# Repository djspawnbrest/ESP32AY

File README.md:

# ZxPod - multiformat Turbo Sound player
ESP32 based AY Turbo Sound multiformat player

## Fast flash firmware avaliable on [Alex Spawn OTA web page](https://ota.alexspawn.ru)

## Starting with firmware version 3.41 - added support for external DAC's - read [External DAC](PCB/ExternalDAC)

## IMPORTANT:
Firmwares from version 3.4 supports only PCB revision C! But you can soldering upgrade revision A and B to C:

Cut JP1 jumper on revisions A and B first!

### From rev.A to B and C:
You need to cut the input track on the resistor R33(see Pic.2) and solder the wire from the ESP32 (see Pic.1) to the cut contact of the resistor. See the images below.

### From rev. A and B to C:
You need to cut the tracks as shown in Figure 5 (red cut lines), then carefully strip the tracks from the solder mask and solder the wires (green lines) to the ESP32.

## Features
### Supported formats:
- .ayl - [Ay_Emul](https://bulba.untergrund.net/emulator_e.htm) by Sergey Bulba own playlist format
- .pt1 - Pro Tracker v1 file format
- .pt2 - Pro Tracker v2 file format
- .pt3 - Pro Tracker v3 (include Turbo Sound on two AY chips) file format
- .stc - Sound Tracker file format
- .stp - Sound Tracker Pro file format
- .asc - Sound Master file format 
- .psc - Pro Sound Creator file format
- .sqt - SQ Tracker file format
- .ay  - AY file format
- .psg - Programmable Sound Generator file format
- .rsf - Registers Stream Flow file format
- .yrg - [Custom AVR-AY format](https://www.avray.ru/ru/avr-ay-player/)
- .mod - Amiga MOD tracker format designed for creating, storing and playing music on an Amiga PC
- .s3m - (Scream Tracker 3 Module) is a module file format, based on the original MOD format used on the Amiga computer.
- .xm  - The XM file format, also known as Extended Module, is a digital audio file type for music created in the FastTracker 2 software (rev.D and above only).
- .tap - A file format for emulating ZX Spectrum magnetic tape images, which stores data from standard Sinclair BASIC procedures for working with a cassette.
- .tzx - A file format used to store programs and games for the ZX Spectrum computer as audio data from magnetic tape.
- .mp3 - MP3 (MPEG-1 Audio Layer 3) is a widely used digital audio format that uses a lossy compression method to significantly reduce file size while maintaining near-CD quality audio.
- .wav - is an audio file format for storing uncompressed audio data, developed by Microsoft and IBM. It is known for high-quality audio that retains all original data, but results in large file sizes, making it popular for professional audio recording and editing. The format stores audio data in chunks and commonly uses linear pulse-code modulation (LPCM) for encoding.
- UART mode (available in player settings menu as Player source)
- SD forwarding via USB as Mass Storage device (rev.D and above only) (press left button("-") and turn ON player)

### Controls
- Before player turning on - hold left button and turn on player to enter root config (needed for change encoder type). Encoder types:
    1. STEP 4L - active low (pull-up to VCC). Full cycle (4 phases) per click.
    2. STEP 4H - active high (pull-up to GND). Full cycle (4 phases) per click
    3. STEP 2 - half cycle (2 phases) per click (Set by default)
    4. STEP 1 - quarter cycle (1 phase) per click, and non-latching encoders
- Before player turning on - hold right button and turn on player to reset config to default.
- Before player turning on - hold encoder button and turn on player to reset last playing track (if player freezes or reboot on this file).
- Encoder Hold - change mode player/file browser
- Encoder Click - in player mode - play/pause; in file browser mode select track/playlist/directory; select - in config mode
- Encoder Double click - in player mode - open settings
- Encoder Push and turn right - fast forward (for ay format change next subsong, for tape formats - change next block)
- Encoder Push and turn left - slow down (for ay format change previous subsong, for tape formats - change previous block)
- Left button click/hold - volume - (in player mode); cancel - in config mode
- Right button click/hold - volume + (in player mode)
- Left button double click - change AY clock (in player mode) for PSG formats or change stereo panning for formats over DAC (mod,s3m etc.)
- Right button double click - change play mode: all/shuffle/once (in player mode)
- Right button hold and encoder click - remove file (only files, only in file browser).
- Right button click - change file sorting in file browser. (only in file browser).

### Playing modes:
- Playing all tracks (in folder/playlist)
- Playing random track (in folder/playlist)
- Playing once track (loop)

### Supports fully realtime file browser

### Supports realtime AY layers change:
- ABC
- ACB
- BAC
- BCA
- CAB
- CBA

### Supports realtime AY clock change:
- ZX SPECTRUM - 1773400 Hz
- PENTAGON - 1750000 Hz
- MSX - 1789772 Hz
- CPC - 1000000 Hz
- ATARI ST - 2000000 Hz

### Built-in battery

### Built-in charger and indication on LED and TFT

### Built-in headphones stereo amplifier controlled by I2C bus

## Demo video with digital sound record:

### UPD 22.10.2024
- Add new feature: "UART mode" with AVR-AY player through UART.

### UPD 04.03.2025
- Add new formats: .mod and .s3m tracker module formats
- Change PCB to revision C

### UPD 18.06.2025
- Change PCB to revision D (ESP32 chip change to ESP32-S3 (N16R8) chip)

### UPD 16.07.2025
- SD forwarding via USB as Mass Storage device (rev.D and above only)

### UPD 12.09.2025
- Add .xm file format (rev.D and above only). Change Firmware version to 3.5

### UPD 15.10.2025
- Add .tap, .tzx formats to play and loads programms on ZX-Spectrum.

### UPD 08.10.2025
- Add .mp3, .wav formats.

### UPD 10.10.2025
- Add file sorting in file broser on right button click!

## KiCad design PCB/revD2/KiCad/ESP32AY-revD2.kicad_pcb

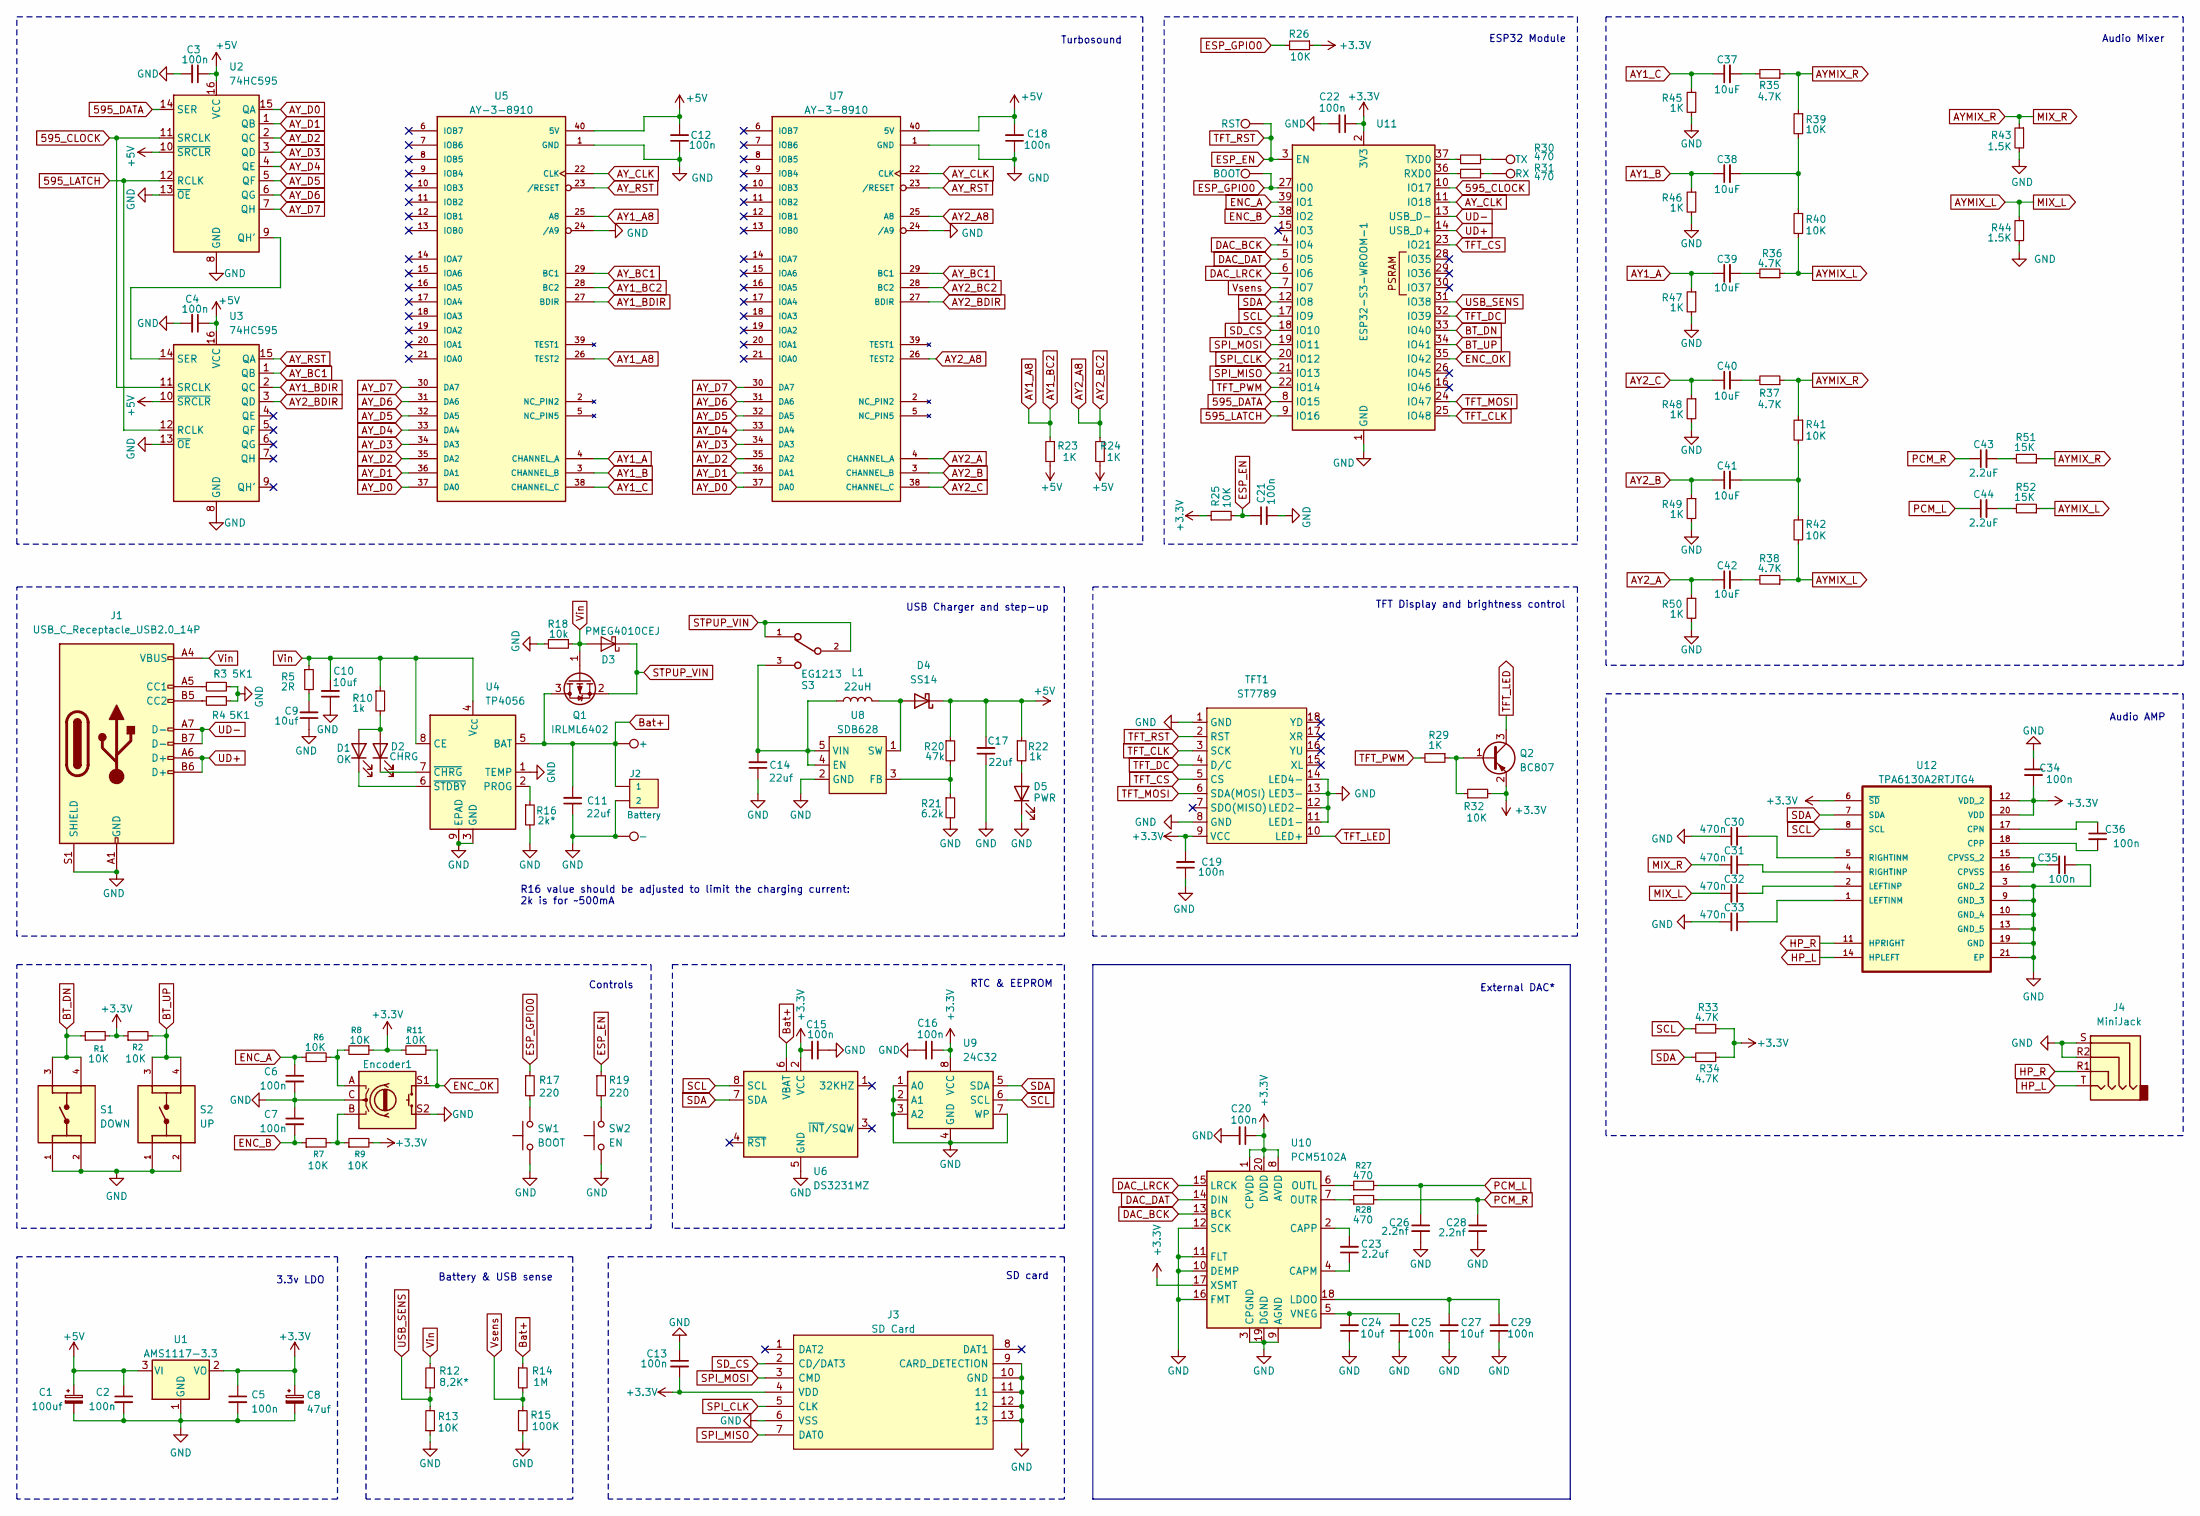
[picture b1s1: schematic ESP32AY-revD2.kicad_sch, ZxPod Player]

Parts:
BAT+1: +; TestPoint_Pad_D3.0mm
BAT-1: -; TestPoint_Pad_D3.0mm
BOOT1: BOOT; TestPoint_Pad_D1.0mm
C1: 100uf; CP_EIA-7343-31_Kemet-D-uni
C2, C3, C4, C5, C6, C7, C12, C13, C15, C16, C18, C19, C20, C21, C22, C25, C29, C34, C35, C36: 100n; C_0805_2012Metric_Pad1.18x1.45mm_HandSolder
C8: 47uf; CP_EIA-7343-31_Kemet-D-uni
C9, C10, C24, C27: 10uf; C_0805_2012Metric_Pad1.18x1.45mm_HandSolder
C11, C14, C17: 22uf; C_1206_3216Metric_Pad1.33x1.80mm_HandSolder
C23: 2.2uf; C_0805_2012Metric_Pad1.18x1.45mm_HandSolder
C26, C28: 2.2nf; C_0805_2012Metric_Pad1.18x1.45mm_HandSolder
C30, C31, C32, C33: 470n; C_0805_2012Metric_Pad1.18x1.45mm_HandSolder
C37, C38, C39, C40, C41, C42: 10uF; C_0805_2012Metric_Pad1.18x1.45mm_HandSolder
C43, C44: 2.2uF; C_0805_2012Metric_Pad1.18x1.45mm_HandSolder
D1: OK; LED_0805_2012Metric
D2: CHRG; LED_0805_2012Metric
D3: PMEG4010CEJ; D_SOD-323F
D4: SS14; D_SMA
D5: PWR; LED_0805_2012Metric
Encoder1: RotaryEncoder_Switch; RotaryEncoder_Alps_EC11E-Switch_Vertical_H20mm
J1: USB_C_Receptacle_USB2.0_14P; USB_C_Receptacle_G-Switch_GT-USB-7010ASV
J2: Battery; JST_PH_S2B-PH-K_1x02_P2.00mm_Horizontal
J3: SD Card; TFP09212B; Manufacturer_Part_Number TFP09-2-12B
J4: MiniJack; AUDIO_JACK_3.5MM_SMD_TRRS_rounded_mixed
L1: 22uH; L_Bourns_SRN8040TA
Q1: IRLML6402; SOT-23
Q2: BC807; SOT-23
R1, R2, R6, R7, R8, R9, R11, R13, R25, R26, R32, R39, R40, R41, R42: 10K; R_0805_2012Metric_Pad1.20x1.40mm_HandSolder
R3, R4: 5K1; R_0805_2012Metric_Pad1.20x1.40mm_HandSolder
R5: 2R; R_0805_2012Metric_Pad1.20x1.40mm_HandSolder
R10, R22: 1k; R_0805_2012Metric_Pad1.20x1.40mm_HandSolder
R12: 8,2К*; R_0805_2012Metric_Pad1.20x1.40mm_HandSolder
R14: 1M; R_0805_2012Metric_Pad1.20x1.40mm_HandSolder
R15: 100K; R_0805_2012Metric_Pad1.20x1.40mm_HandSolder
R16: 2k*; R_0805_2012Metric_Pad1.20x1.40mm_HandSolder
R17, R19: 220; R_0805_2012Metric_Pad1.20x1.40mm_HandSolder
R18: 10k; R_0805_2012Metric_Pad1.20x1.40mm_HandSolder
R20: 47k; R_0805_2012Metric_Pad1.20x1.40mm_HandSolder
R21: 6.2k; R_0805_2012Metric_Pad1.20x1.40mm_HandSolder
R23, R24, R29, R45, R46, R47, R48, R49, R50: 1K; R_0805_2012Metric_Pad1.20x1.40mm_HandSolder
R27, R28, R30, R31: 470; R_0805_2012Metric_Pad1.20x1.40mm_HandSolder
R33, R34, R35, R36, R37, R38: 4.7K; R_0805_2012Metric_Pad1.20x1.40mm_HandSolder
R43, R44: 1.5K; R_0805_2012Metric_Pad1.20x1.40mm_HandSolder
R51, R52: 15K; R_0805_2012Metric_Pad1.20x1.40mm_HandSolder
RST1: RST; TestPoint_Pad_D1.0mm
RX1: RX; TestPoint_Pad_D1.0mm
S1: DOWN; SW_Push_1P1T_NO_6x6mm_H9.5mm
S2: UP; SW_Push_1P1T_NO_6x6mm_H9.5mm
S3: EG1213; SW_EG1213
SW1: BOOT; SW_SPST_PTS810_handsoldering
SW2: EN; SW_SPST_PTS810_handsoldering
TFT1: ST7789
TX1: TX; TestPoint_Pad_D1.0mm
U1: AMS1117-3.3; SOT-223-3_TabPin2
U2, U3: 74HC595; SO-16_3.9x9.9mm_P1.27mm
U4: TP4056; SOIC-8-1EP_3.9x4.9mm_P1.27mm_EP2.41x3.3mm_ThermalVias
U5, U7: AY-3-8910; DIP-40_W15.24mm_Socket
U6: DS3231MZ; SOIC-8_3.9x4.9mm_P1.27mm
U8: SDB628; SOT-23-6_Handsoldering
U9: 24С32; SOIC-8_3.9x4.9mm_P1.27mm
U10: PCM5102A; TSSOP-20_4.4x6.5mm_P0.65mm
U11: ESP32-S3-WROOM-1
U12: TPA6130A2RTJTG4; QFN50P400X400X80-21N; MPN TPA6130A2RTJTG4

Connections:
595_CLOCK: U2.11 (SRCLK), U3.11 (SRCLK), U11.10 (IO17)
595_DATA: U2.14 (SER), U11.8 (IO15)
595_LATCH: U2.12 (RCLK), U3.12 (RCLK), U11.9 (IO16)
+3.3V: C5.1, C8.1, C13.2, C15.1, C16.1, C19.2, C20.1, C22.1, C34.2, J3.4 (VDD), Q2.2 (E), R1.2, R2.1, R8.1, R9.2, R11.2, R25.1, R26.1, R32.2, R33.1, R34.1, TFT1.9 (VCC), U1.2 (VO), U6.2 (VCC), U9.8 (VCC), U10.1 (CPVDD), U10.8 (AVDD), U10.17 (XSMT), U10.20 (DVDD), U11.2 (3V3), U12.6 (~SD), U12.12 (VDD_2), U12.20 (VDD)
+5V: C1.1, C2.1, C3.1, C4.1, C12.2, C17.2, C18.2, D4.1 (K), R20.1, R22.1, R23.2, R24.2, U1.3 (VI), U2.10 (~SRCLR), U2.16 (VCC), U3.10 (~SRCLR), U3.16 (VCC), U5.40 (5V), U7.40 (5V)
AY1_A: C39.1, R47.1, U5.4 (CHANNEL_A)
AY1_A8: R23.1, U5.25 (A8), U5.26 (TEST2), U5.28 (BC2)
AY1_B: C38.1, R46.1, U5.3 (CHANNEL_B)
AY1_BDIR: U3.2 (QC), U5.27 (BDIR)
AY1_C: C37.1, R45.1, U5.38 (CHANNEL_C)
AY2_A: C42.1, R50.1, U7.4 (CHANNEL_A)
AY2_A8: R24.1, U7.25 (A8), U7.26 (TEST2), U7.28 (BC2)
AY2_B: C41.1, R49.1, U7.3 (CHANNEL_B)
AY2_BDIR: U3.3 (QD), U7.27 (BDIR)
AY2_C: C40.1, R48.1, U7.38 (CHANNEL_C)
AY_BC1: U3.1 (QB), U5.29 (BC1), U7.29 (BC1)
AY_CLK: U5.22 (CLK), U7.22 (CLK), U11.11 (IO18)
AY_D0: U2.15 (QA), U5.37 (DA0), U7.37 (DA0)
AY_D1: U2.1 (QB), U5.36 (DA1), U7.36 (DA1)
AY_D2: U2.2 (QC), U5.35 (DA2), U7.35 (DA2)
AY_D3: U2.3 (QD), U5.34 (DA3), U7.34 (DA3)
AY_D4: U2.4 (QE), U5.33 (DA4), U7.33 (DA4)
AY_D5: U2.5 (QF), U5.32 (DA5), U7.32 (DA5)
AY_D6: U2.6 (QG), U5.31 (DA6), U7.31 (DA6)
AY_D7: U2.7 (QH), U5.30 (DA7), U7.30 (DA7)
AY_RST: U3.15 (QA), U5.23 (/RESET), U7.23 (/RESET)
BT_DN: R1.1, S1.3, S1.4, U11.33 (IO40)
BT_UP: R2.2, S2.3, S2.4, U11.34 (IO41)
Bat+: BAT+1.1 (1_1), C11.2, J2.1, Q1.3 (D), R14.1, U4.5 (BAT), U6.6 (VBAT)
DAC_BCK: U10.13 (BCK), U11.4 (IO4)
DAC_DAT: U10.14 (DIN), U11.5 (IO5)
DAC_LRCK: U10.15 (LRCK), U11.6 (IO6)
ENC_A: C6.1, R6.1, U11.39 (IO1)
ENC_B: C7.2, R7.1, U11.38 (IO2)
ENC_OK: Encoder1.S1, R11.1, U11.35 (IO42)
ESP_EN: C21.1, R19.1, R25.2, RST1.1 (1_1), TFT1.2 (RST), U11.3 (EN)
ESP_GPIO0: BOOT1.1 (1_1), R17.1, R26.2, U11.27 (IO0)
GND: BAT-1.1 (1_1), C1.2, C2.2, C3.2, C4.2, C5.2, C6.2, C7.1, C8.2, C9.1, C10.1, C11.1, C12.1, C13.1, C14.1, C15.2, C16.2, C17.1, C18.1, C19.1, C20.2, C21.2, C22.2, C24.1, C25.1, C26.2, C27.1, C28.2, C29.1, C30.1, C33.2, C34.1, C35.1, D5.1 (K), Encoder1.C, Encoder1.MP, Encoder1.S2, J1.A1 (GND), J1.A12 (GND), J1.B1 (GND), J1.B12 (GND), J1.S1 (SHIELD), J2.2, J3.6 (VSS), J3.9 (CARD_DETECTION), J3.10 (GND), J3.11, J3.12, J3.13, J4.R2, J4.S, R3.2, R4.2, R13.1, R15.2, R16.2, R18.2, R21.2, R43.2, R44.2, R45.2, R46.2, R47.2, R48.2, R49.2, R50.2, S1.1, S1.2, S2.1, S2.2, SW1.1 (A), SW2.1 (A), TFT1.1 (GND), TFT1.8 (GND), TFT1.11 (LED1-), TFT1.12 (LED2-), TFT1.13 (LED3-), TFT1.14 (LED4-), U1.1 (GND), U2.8 (GND), U2.13 (~OE), U3.8 (GND), U3.13 (~OE), U4.1 (TEMP), U4.3 (GND), U4.9 (EPAD), U5.1 (GND), U5.24 (/A9), U6.5 (GND), U7.1 (GND), U7.24 (/A9), U8.2 (GND), U9.1 (A0), U9.2 (A1), U9.3 (A2), U9.4 (GND), U9.7 (WP), U10.3 (CPGND), U10.9 (AGND), U10.10 (DEMP), U10.11 (FLT), U10.12 (SCK), U10.16 (FMT), U10.19 (DGND), U11.1 (GND), U11.40 (GND), U11.41 (GND), U12.3 (GND_2), U12.9 (GND_3), U12.10 (GND_4), U12.13 (GND_5), U12.19 (GND), U12.21 (EP)
HP_L: J4.T, U12.14 (HPLEFT)
HP_R: J4.R1, U12.11 (HPRIGHT)
unnamed: C9.2, R5.2
unnamed: C37.2, R35.2
unnamed: C38.2, R39.2, R40.1
unnamed: C39.2, R36.2
unnamed: C40.2, R37.2
unnamed: C41.2, R41.2, R42.1
unnamed: C42.2, R38.2
unnamed: C43.2, R51.2
unnamed: C44.2, R52.2
unnamed: D1.2 (A), D2.2 (A), R10.2
unnamed: D1.1 (K), U4.6 (~STDBY)
unnamed: D2.1 (K), U4.7 (~CHRG)
unnamed: D4.2 (A), L1.2, U8.1 (SW)
unnamed: D5.2 (A), R22.2
unnamed: Encoder1.A, R6.2, R8.2
unnamed: Encoder1.B, R7.2, R9.1
unnamed: J1.A5 (CC1), R3.1
unnamed: J1.B5 (CC2), R4.1
unnamed: Q2.1 (B), R29.1, R32.1
unnamed: R30.1, TX1.1 (1_1)
unnamed: R31.1, RX1.1 (1_1)
unnamed: R17.2, SW1.2 (B)
unnamed: R19.2, SW2.2 (B)
unnamed: U2.9 (QH'), U3.14 (SER)
unnamed: R16.1, U4.2 (PROG)
unnamed: C14.2, L1.1, S3.3, U8.4 (EN), U8.5 (VIN)
unnamed: R20.2, R21.1, U8.3 (FB)
unnamed: C23.1, U10.4 (CAPM)
unnamed: C23.2, U10.2 (CAPP)
unnamed: C27.2, C29.2, U10.18 (LDOO)
unnamed: R27.1, U10.6 (OUTL)
unnamed: R28.1, U10.7 (OUTR)
unnamed: C24.2, C25.2, U10.5 (VNEG)
unnamed: R31.2, U11.36 (RXD0)
unnamed: R30.2, U11.37 (TXD0)
unnamed: C36.1, U12.17 (CPN)
unnamed: C36.2, U12.18 (CPP)
unnamed: C35.2, U12.15 (CPVSS_2), U12.16 (CPVSS)
unnamed: C33.1, U12.1 (LEFTINM)
unnamed: C32.1, U12.2 (LEFTINP)
unnamed: C30.2, U12.5 (RIGHTINM)
unnamed: C31.1, U12.4 (RIGHTINP)
SCL: R33.2, U6.8 (SCL), U9.6 (SCL), U11.17 (IO9), U12.8 (SCL)
SDA: R34.2, U6.7 (SDA), U9.5 (SDA), U11.12 (IO8), U12.7 (SDA)
SD_CS: J3.2 (CD/DAT3), U11.18 (IO10)
SPI_CLK: J3.5 (CLK), U11.20 (IO12)
SPI_MISO: J3.7 (DAT0), U11.21 (IO13)
SPI_MOSI: J3.3 (CMD), U11.19 (IO11)
STPUP_VIN: D3.1 (K), Q1.2 (S), S3.1, S3.2
TFT_CLK: TFT1.3 (SCK), U11.25 (IO48)
TFT_CS: TFT1.5 (CS), U11.23 (IO21)
TFT_DC: TFT1.4 (D/C), U11.32 (IO39)
TFT_LED: Q2.3 (C), TFT1.10 (LED+)
TFT_MOSI: TFT1.6 (SDA(MOSI)), U11.24 (IO47)
TFT_PWM: R29.2, U11.22 (IO14)
UD+: J1.A6 (D+), J1.B6 (D+), U11.14 (USB_D+)
UD-: J1.A7 (D-), J1.B7 (D-), U11.13 (USB_D-)
USB_SENS: R12.1, R13.2, U11.31 (IO38)
Vin: C10.2, D3.2 (A), J1.A4 (VBUS), J1.A9 (VBUS), J1.B4 (VBUS), J1.B9 (VBUS), Q1.1 (G), R5.1, R10.1, R12.2, R18.1, U4.4 (V_{CC}), U4.8 (CE)
Vsens: R14.2, R15.1, U11.7 (IO7)

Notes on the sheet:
Battery & USB sense
TFT Display and brightness control
ESP32 Module
RTC & EEPROM
SD card
Turbosound
Audio AMP
External DAC*
USB Charger and step-up
3.3v LDO
R16 value should be adjusted to limit the charging current: 2k is for ~500mA
Controls
Audio Mixer

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
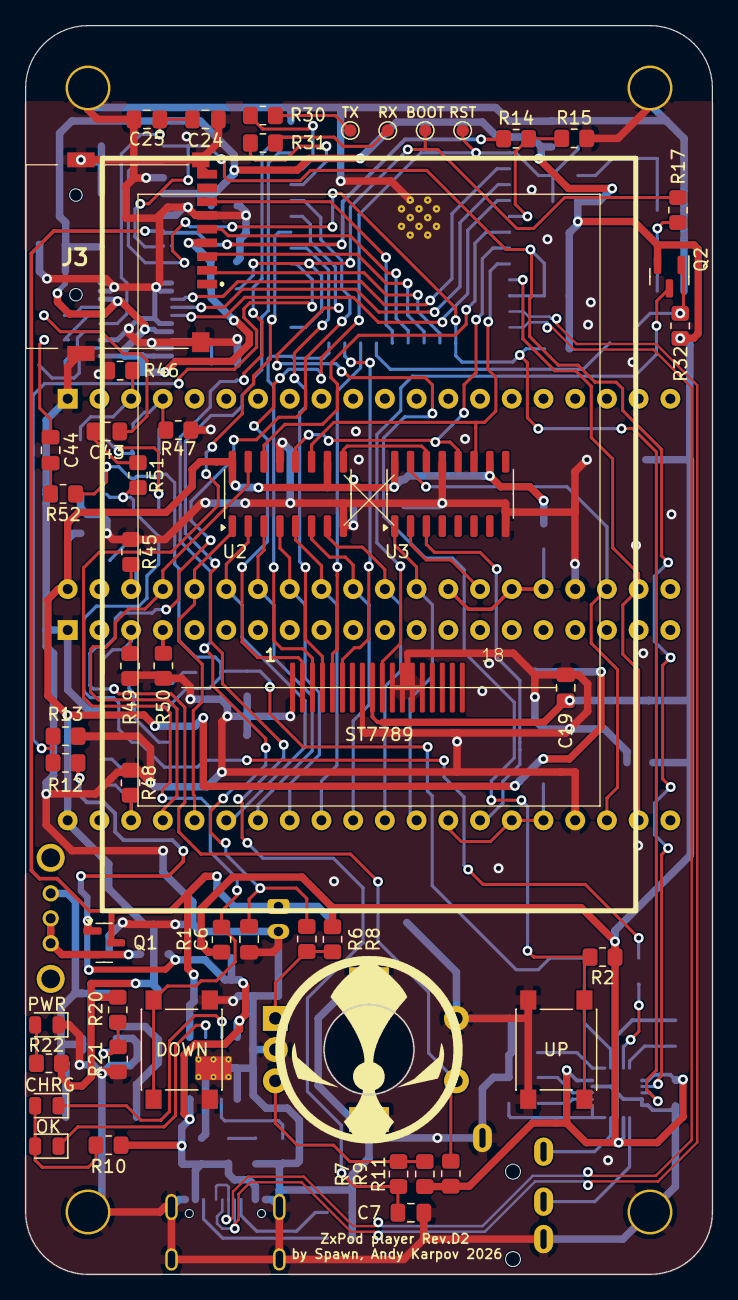
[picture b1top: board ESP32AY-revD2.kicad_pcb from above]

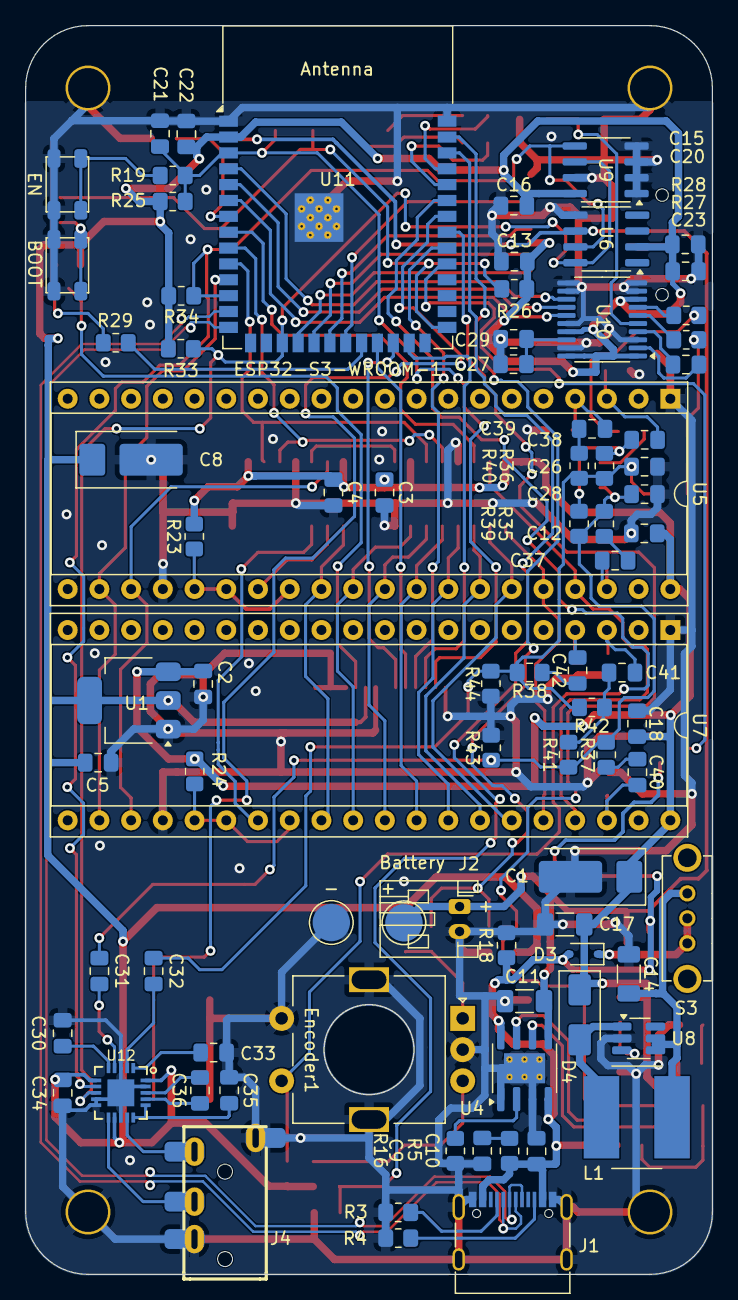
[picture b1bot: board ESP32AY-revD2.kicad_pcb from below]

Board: 2 copper layers, 55.0 x 100.0 mm, 133 parts (83 on the bottom side), 104 nets.

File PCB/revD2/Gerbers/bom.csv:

Designator,Footprint,Quantity,Value,LCSC Part #
C1,CP_EIA-7343-31_Kemet-D-uni,1,100uf,
"C10, C24, C27, C37, C38, C39, C40, C41, C42, C9",0805,10,10uf,
"C11, C14, C17",1206,3,22uf,
"C12, C13, C15, C16, C18, C19, C2, C20, C21, C22, C25, C29, C3, C34, C35, C36, C4, C5, C6, C7",0805,20,100n,
"C23, C43, C44",0805,3,2.2uf,
"C26, C28",0805,2,2.2nf,
"C30, C31, C32, C33",0805,4,470n,
C8,CP_EIA-7343-31_Kemet-D-uni,1,47uf,
D1,0805,1,OK,
D2,0805,1,CHRG,
D3,D_SOD-323F,1,PMEG4010CEJ,
D4,D_SMA,1,SS14,
D5,0805,1,PWR,
ENCODER1,RotaryEncoder_Alps_EC11E-Switch_Vertical_H20mm,1,RotaryEncoder_Switch,
J1,USB_C_Receptacle_G-Switch_GT-USB-7010ASV,1,USB_C_Receptacle_USB2.0_14P,
J2,JST_PH_S2B-PH-K_1x02_P2.00mm_Horizontal,1,Battery,
J3,TFP09212B,1,SD Card,
J4,AUDIO_JACK_3.5MM_SMD_TRRS_rounded_mixed,1,MiniJack,
L1,L_Bourns_SRN8040TA,1,22uH,
Q1,SOT-23,1,IRLML6402,
Q2,SOT-23,1,BC807,
"R1, R11, R13, R18, R2, R25, R26, R32, R39, R40, R41, R42, R6, R7, R8, R9",0805,16,10K,
"R10, R22, R23, R24, R29, R45, R46, R47, R48, R49, R50",0805,11,1k,
R12,0805,1,"8,2К*",
R14,0805,1,1M,
R15,0805,1,100K,
R16,0805,1,2k*,
"R17, R19",0805,2,220,
R20,0805,1,47k,
R21,0805,1,6.2k,
"R27, R28, R30, R31",0805,4,470,
"R3, R4",0805,2,5K1,
"R33, R34, R35, R36, R37, R38",0805,6,4.7K,
"R43, R44",0805,2,1.5K,
R5,0805,1,2R,
"R51, R52",0805,2,15K,
S1,SW_Push_1P1T_NO_6x6mm_H9.5mm,1,DOWN,
S2,SW_Push_1P1T_NO_6x6mm_H9.5mm,1,UP,
S3,SW_EG1213,1,EG1213,
SW1,SW_SPST_PTS810_handsoldering,1,BOOT,
SW2,SW_SPST_PTS810_handsoldering,1,EN,
TFT1,ST7789,1,ST7789,
U1,SOT-223-3_TabPin2,1,AMS1117-3.3,
U10,TSSOP-20_4.4x6.5mm_P0.65mm,1,PCM5102A,
U11,ESP32-S3-WROOM-1,1,ESP32-S3-WROOM-1,
U12,QFN50P400X400X80-21N,1,TPA6130A2RTJTG4,TPA6130A2RTJTG4
"U2, U3",SO-16_3.9x9.9mm_P1.27mm,2,74HC595,
U4,SOIC-8-1EP_3.9x4.9mm_P1.27mm_EP2.41x3.3mm_ThermalVias,1,TP4056,
"U5, U7",DIP-40_W15.24mm_Socket,2,AY-3-8910,
U6,SOIC-8_3.9x4.9mm_P1.27mm,1,DS3231MZ,
U8,SOT-23-6_Handsoldering,1,SDB628,
U9,SOIC-8_3.9x4.9mm_P1.27mm,1,24С32,

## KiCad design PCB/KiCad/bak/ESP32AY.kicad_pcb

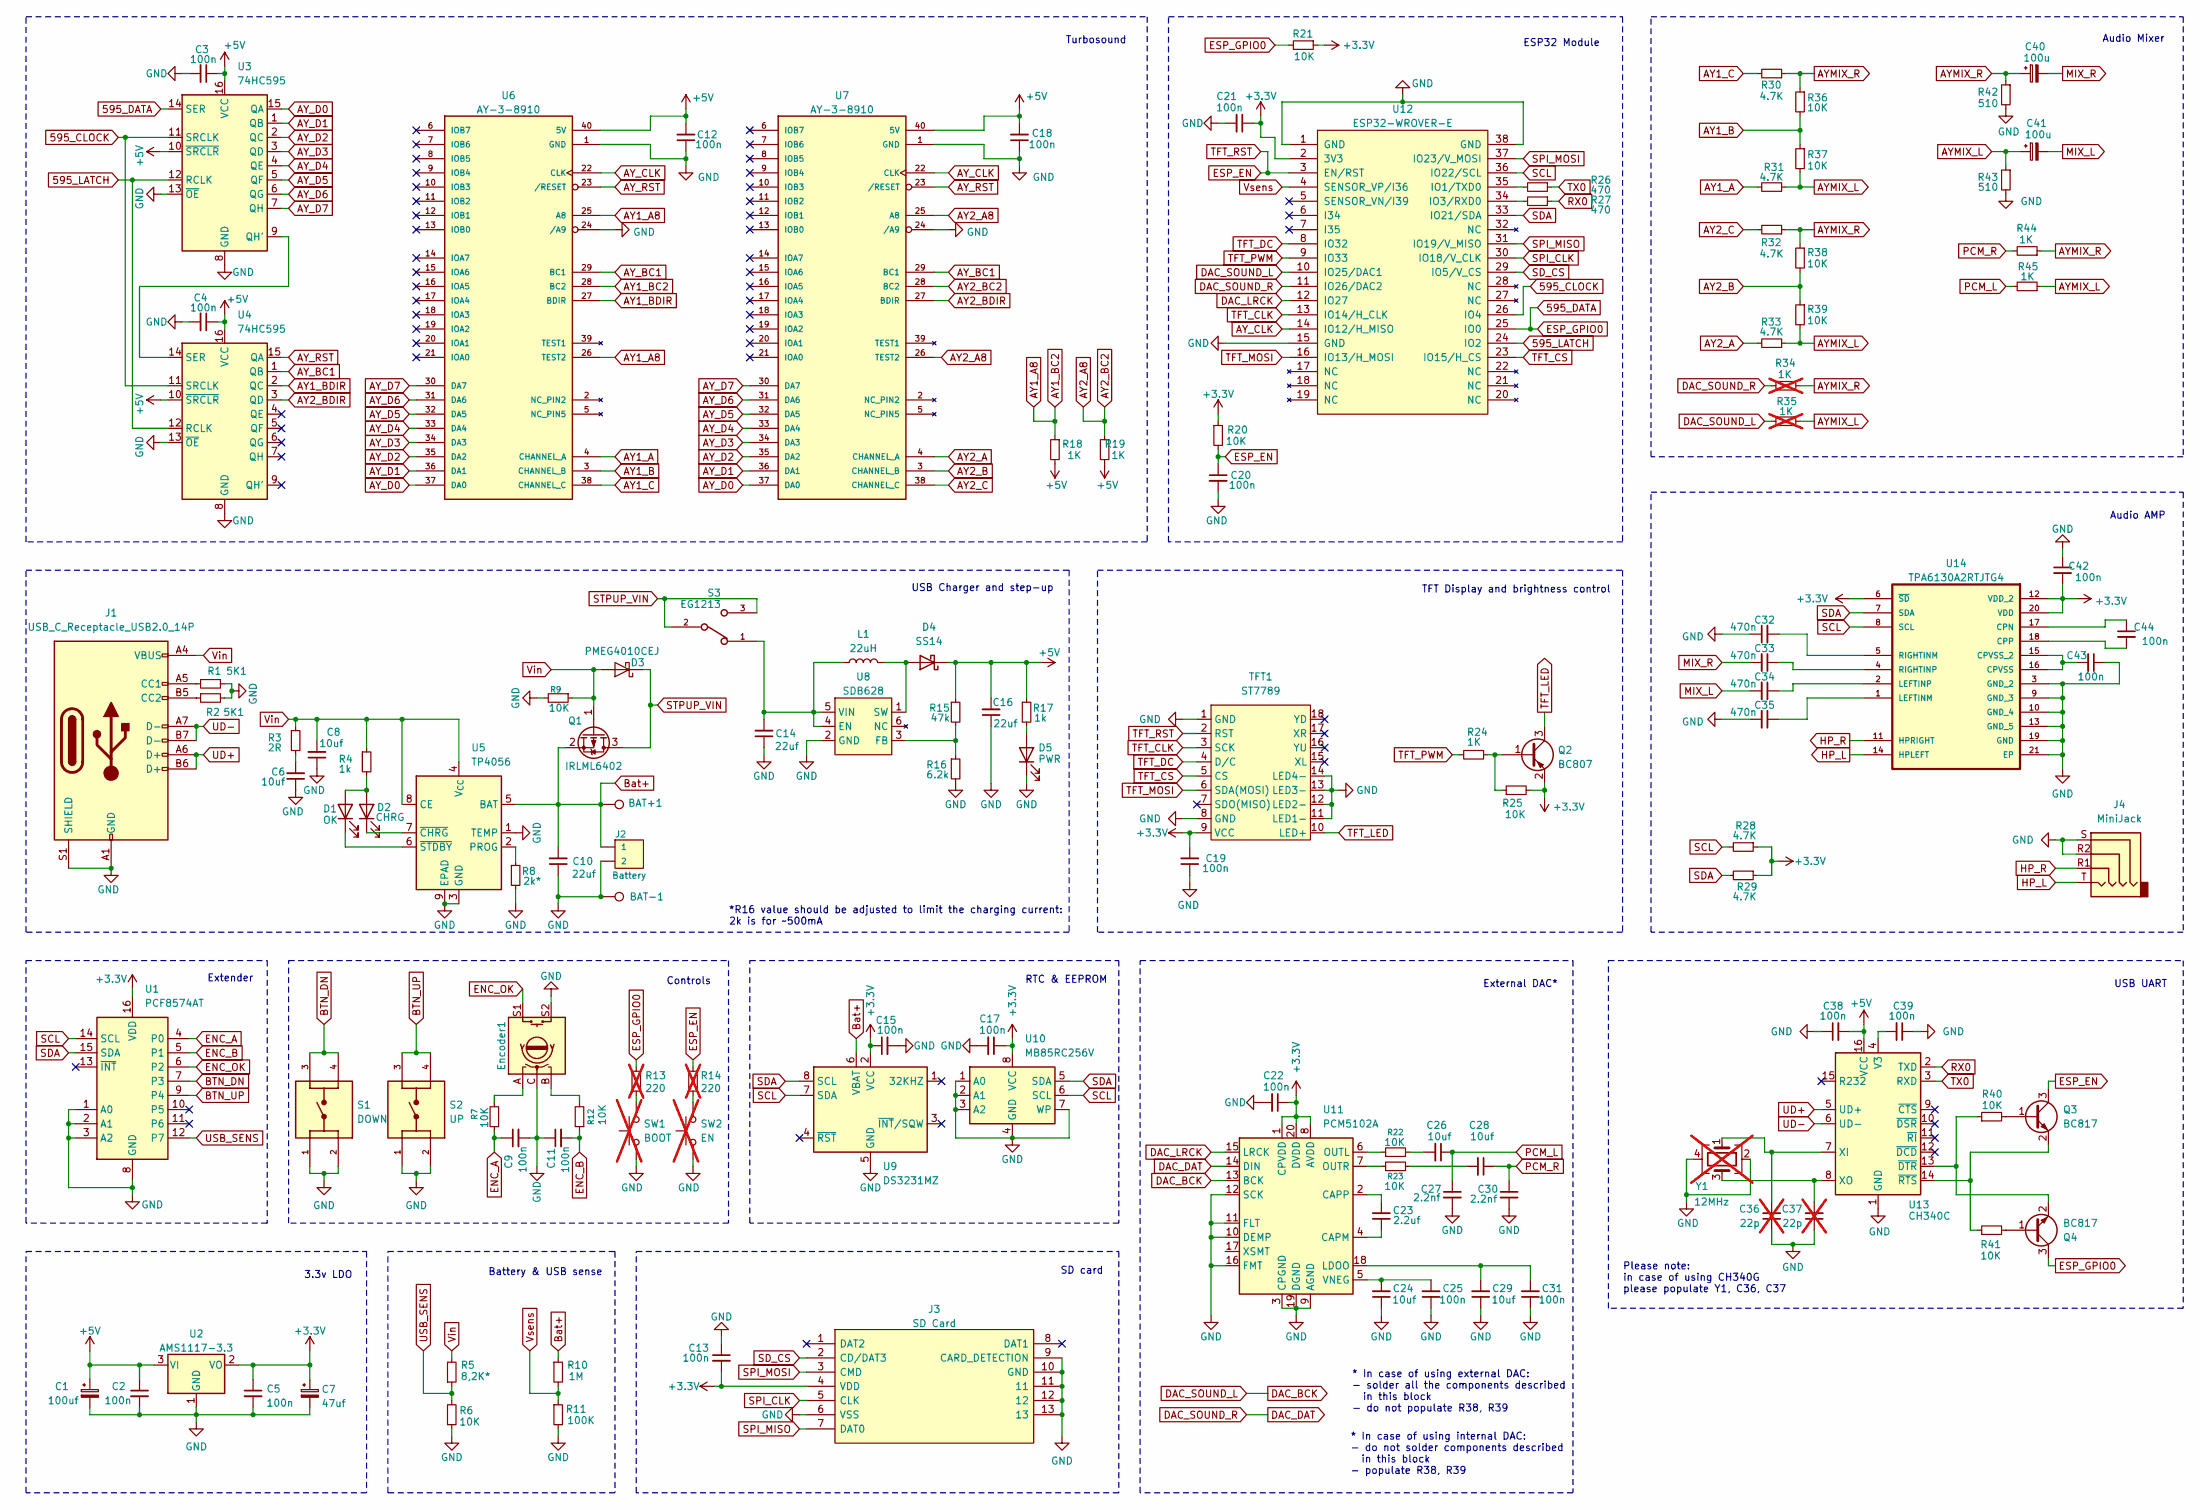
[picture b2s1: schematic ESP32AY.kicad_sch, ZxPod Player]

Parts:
BAT+1: +; TestPoint_Pad_D3.0mm
BAT-1: -; TestPoint_Pad_D3.0mm
C1: 100uf; CP_EIA-7343-31_Kemet-D-uni
C2, C3, C4, C5, C9, C11, C12, C13, C15, C17, C18, C19, C20, C21, C22, C25, C31, C38, C39, C42, C43, C44: 100n; C_0805_2012Metric_Pad1.18x1.45mm_HandSolder
C6, C8, C24, C26, C28, C29: 10uf; C_0805_2012Metric_Pad1.18x1.45mm_HandSolder
C7: 47uf; CP_EIA-7343-31_Kemet-D-uni
C10, C14, C16: 22uf; C_1206_3216Metric_Pad1.33x1.80mm_HandSolder
C23: 2.2uf; C_0805_2012Metric_Pad1.18x1.45mm_HandSolder
C27, C30: 2.2nf; C_0805_2012Metric_Pad1.18x1.45mm_HandSolder
C32, C33, C34, C35: 470n; C_0805_2012Metric_Pad1.18x1.45mm_HandSolder
C36, C37: 22p; C_0805_2012Metric_Pad1.18x1.45mm_HandSolder; not fitted
C40, C41: 100u; CP_EIA-7343-31_Kemet-D_Pad2.25x2.55mm_HandSolder
D1: OK; LED_0805_2012Metric
D2: CHRG; LED_0805_2012Metric
D3: PMEG4010CEJ; D_SOD-323F
D4: SS14; D_SMA
D5: PWR; LED_0805_2012Metric
Encoder1: RotaryEncoder_Switch; RotaryEncoder_Alps_EC11E-Switch_Vertical_H20mm
J1: USB_C_Receptacle_USB2.0_14P; USB_C_Receptacle_G-Switch_GT-USB-7010ASV
J2: Battery; JST_PH_S2B-PH-K_1x02_P2.00mm_Horizontal
J3: SD Card; TFP09212B; Manufacturer_Part_Number TFP09-2-12B
J4: MiniJack; AUDIO_JACK_3.5MM_SMD_TRRS_rounded_mixed
L1: 22uH; L_Bourns_SRN8040TA
Q1: IRLML6402; SOT-23
Q2: BC807; SOT-23
Q3, Q4: BC817; SOT-23
R1, R2: 5K1; R_0805_2012Metric_Pad1.20x1.40mm_HandSolder
R3: 2R; R_0805_2012Metric_Pad1.20x1.40mm_HandSolder
R4, R17: 1k; R_0805_2012Metric_Pad1.20x1.40mm_HandSolder
R5: 8,2К*; R_0805_2012Metric_Pad1.20x1.40mm_HandSolder
R6, R7, R9, R12, R20, R21, R22, R23, R25, R36, R37, R38, R39, R40, R41: 10K; R_0805_2012Metric_Pad1.20x1.40mm_HandSolder
R8: 2k*; R_0805_2012Metric_Pad1.20x1.40mm_HandSolder
R10: 1M; R_0805_2012Metric_Pad1.20x1.40mm_HandSolder
R11: 100K; R_0805_2012Metric_Pad1.20x1.40mm_HandSolder
R13, R14: 220; R_0805_2012Metric_Pad1.20x1.40mm_HandSolder; not fitted
R15: 47k; R_0805_2012Metric_Pad1.20x1.40mm_HandSolder
R16: 6.2k; R_0805_2012Metric_Pad1.20x1.40mm_HandSolder
R18, R19, R24, R44, R45: 1K; R_0805_2012Metric_Pad1.20x1.40mm_HandSolder
R26, R27: 470; R_0805_2012Metric_Pad1.20x1.40mm_HandSolder
R28, R29, R30, R31, R32, R33: 4.7K; R_0805_2012Metric_Pad1.20x1.40mm_HandSolder
R34, R35: 1K; R_0805_2012Metric_Pad1.20x1.40mm_HandSolder; not fitted
R42, R43: 510; R_0805_2012Metric_Pad1.20x1.40mm_HandSolder
S1: DOWN; SW_Push_1P1T_NO_6x6mm_H9.5mm
S2: UP; SW_Push_1P1T_NO_6x6mm_H9.5mm
S3: EG1213; SW_EG1213
SW1: BOOT; SW_SPST_PTS810_handsoldering; not fitted
SW2: EN; SW_SPST_PTS810_handsoldering; not fitted
TFT1: ST7789
U1: PCF8574AT; SOIC-16W_7.5x10.3mm_P1.27mm
U2: AMS1117-3.3; SOT-223-3_TabPin2
U3, U4: 74HC595; SO-16_3.9x9.9mm_P1.27mm
U5: TP4056; SOIC-8-1EP_3.9x4.9mm_P1.27mm_EP2.41x3.3mm_ThermalVias
U6, U7: AY-3-8910; DIP-40_W15.24mm_Socket
U8: SDB628; SOT-23-6_Handsoldering
U9: DS3231MZ; SOIC-8_3.9x4.9mm_P1.27mm
U10: MB85RC256V; SOIC-8_3.9x4.9mm_P1.27mm
U11: PCM5102A; TSSOP-20_4.4x6.5mm_P0.65mm
U12: ESP32-WROVER-E; ESP32-WROVER-IE
U13: CH340C; SOIC-16_3.9x9.9mm_P1.27mm
U14: TPA6130A2RTJTG4; QFN50P400X400X80-21N; MPN TPA6130A2RTJTG4
Y1: 12MHz; Crystal_SMD_3225-4Pin_3.2x2.5mm_HandSoldering; PARTREV 10/24/2022; not fitted

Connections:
595_CLOCK: U3.11 (SRCLK), U4.11 (SRCLK), U12.26 (IO4)
595_DATA: Q4.3 (C), R13.1, R21.2, U3.14 (SER), U12.25 (IO0)
595_LATCH: U3.12 (RCLK), U4.12 (RCLK), U12.24 (IO2)
+3.3V: C5.1, C7.1, C13.2, C15.1, C17.1, C19.2, C21.1, C22.1, C42.2, J3.4 (VDD), Q2.2 (E), R20.1, R21.1, R25.2, R28.1, R29.1, TFT1.9 (VCC), U1.16 (VDD), U2.2 (VO), U9.2 (VCC), U10.8 (VCC), U11.1 (CPVDD), U11.8 (AVDD), U11.20 (DVDD), U12.2 (3V3), U14.6 (~SD), U14.12 (VDD_2), U14.20 (VDD)
+5V: C1.1, C2.1, C3.1, C4.1, C12.2, C16.2, C18.2, C38.2, D4.1 (K), R15.1, R17.1, R18.2, R19.2, U2.3 (VI), U3.10 (~SRCLR), U3.16 (VCC), U4.10 (~SRCLR), U4.16 (VCC), U6.40 (5V), U7.40 (5V), U13.16 (VCC)
AY1_A: R31.2, U6.4 (CHANNEL_A)
AY1_A8: R18.1, U6.25 (A8), U6.26 (TEST2), U6.28 (BC2)
AY1_B: R36.2, R37.1, U6.3 (CHANNEL_B)
AY1_BDIR: U4.2 (QC), U6.27 (BDIR)
AY1_C: R30.2, U6.38 (CHANNEL_C)
AY2_A: R33.2, U7.4 (CHANNEL_A)
AY2_A8: R19.1, U7.25 (A8), U7.26 (TEST2), U7.28 (BC2)
AY2_B: R38.2, R39.1, U7.3 (CHANNEL_B)
AY2_BDIR: U4.3 (QD), U7.27 (BDIR)
AY2_C: R32.2, U7.38 (CHANNEL_C)
AYMIX_L: C41.1, R31.1, R33.1, R35.1, R37.2, R39.2, R43.1, R45.1
AYMIX_R: C40.1, R30.1, R32.1, R34.1, R36.1, R38.1, R42.1, R44.1
AY_BC1: U4.1 (QB), U6.29 (BC1), U7.29 (BC1)
AY_CLK: U6.22 (CLK), U7.22 (CLK), U12.14 (IO12/H_MISO)
AY_D0: U3.15 (QA), U6.37 (DA0), U7.37 (DA0)
AY_D1: U3.1 (QB), U6.36 (DA1), U7.36 (DA1)
AY_D2: U3.2 (QC), U6.35 (DA2), U7.35 (DA2)
AY_D3: U3.3 (QD), U6.34 (DA3), U7.34 (DA3)
AY_D4: U3.4 (QE), U6.33 (DA4), U7.33 (DA4)
AY_D5: U3.5 (QF), U6.32 (DA5), U7.32 (DA5)
AY_D6: U3.6 (QG), U6.31 (DA6), U7.31 (DA6)
AY_D7: U3.7 (QH), U6.30 (DA7), U7.30 (DA7)
AY_RST: U4.15 (QA), U6.23 (/RESET), U7.23 (/RESET)
BTN_DN: S1.3, S1.4, U1.7 (P3)
BTN_UP: S2.3, S2.4, U1.9 (P4)
Bat+: BAT+1.1, C10.2, J2.1, Q1.2 (S), R10.1, U5.5 (BAT), U9.6 (VBAT)
DAC_BCK: R35.2, U11.13 (BCK), U12.10 (IO25/DAC1)
DAC_DAT: R34.2, U11.14 (DIN), U12.11 (IO26/DAC2)
DAC_LRCK: U11.15 (LRCK), U12.12 (IO27)
ENC_A: C9.1, R7.1, U1.4 (P0)
ENC_B: C11.2, R12.1, U1.5 (P1)
ENC_OK: Encoder1.S1, U1.6 (P2)
ESP_EN: C20.1, Q3.3 (C), R14.1, R20.2, TFT1.2 (RST), U12.3 (EN/RST)
GND: BAT-1.1, C1.2, C2.2, C3.2, C4.2, C5.2, C6.1, C7.2, C8.1, C9.2, C10.1, C11.1, C12.1, C13.1, C14.1, C15.2, C16.1, C17.2, C18.1, C19.1, C20.2, C21.2, C22.2, C24.1, C25.1, C27.2, C29.1, C30.2, C31.1, C32.1, C35.2, C36.1, C37.1, C38.1, C39.1, C42.1, C43.1, D5.1 (K), Encoder1.C, Encoder1.MP, Encoder1.S2, J1.A1 (GND), J1.A12 (GND), J1.B1 (GND), J1.B12 (GND), J1.S1 (SHIELD), J2.2, J3.6 (VSS), J3.9 (CARD_DETECTION), J3.10 (GND), J3.11, J3.12, J3.13, J4.R2, J4.S, R1.2, R2.2, R6.1, R8.2, R9.2, R11.2, R16.2, R42.2, R43.2, S1.1, S1.2, S2.1, S2.2, SW1.1 (A), SW2.1 (A), TFT1.1 (GND), TFT1.8 (GND), TFT1.11 (LED1-), TFT1.12 (LED2-), TFT1.13 (LED3-), TFT1.14 (LED4-), U1.1 (A0), U1.2 (A1), U1.3 (A2), U1.8 (GND), U2.1 (GND), U3.8 (GND), U3.13 (~OE), U4.8 (GND), U4.13 (~OE), U5.1 (TEMP), U5.3 (GND), U5.9 (EPAD), U6.1 (GND), U6.24 (/A9), U7.1 (GND), U7.24 (/A9), U8.2 (GND), U9.5 (GND), U10.1 (A0), U10.2 (A1), U10.3 (A2), U10.4 (GND), U10.7 (WP), U11.3 (CPGND), U11.9 (AGND), U11.10 (DEMP), U11.11 (FLT), U11.12 (SCK), U11.16 (FMT), U11.19 (DGND), U12.1 (GND), U12.15 (GND), U12.38 (GND), U12.39, U13.1 (GND), U14.3 (GND_2), U14.9 (GND_3), U14.10 (GND_4), U14.13 (GND_5), U14.19 (GND), U14.21 (EP), Y1.2, Y1.4
HP_L: J4.T, U14.14 (HPLEFT)
HP_R: J4.R1, U14.11 (HPRIGHT)
MIX_L: C34.2, C41.2
MIX_R: C33.2, C40.2
unnamed: C6.2, R3.2
unnamed: C26.2, R22.2
unnamed: C28.2, R23.2
unnamed: D1.2 (A), D2.2 (A), R4.2
unnamed: D1.1 (K), U5.6 (~STDBY)
unnamed: D2.1 (K), U5.7 (~CHRG)
unnamed: D4.2 (A), L1.2, U8.1 (SW)
unnamed: D5.2 (A), R17.2
unnamed: Encoder1.A, R7.2
unnamed: Encoder1.B, R12.2
unnamed: J1.A5 (CC1), R1.1
unnamed: J1.B5 (CC2), R2.1
unnamed: Q2.1 (B), R24.1, R25.1
unnamed: Q3.1 (B), R40.2
unnamed: Q3.2 (E), R41.1, U13.14 (~RTS)
unnamed: Q4.1 (B), R41.2
unnamed: Q4.2 (E), R40.1, U13.13 (~DTR)
unnamed: R13.2, SW1.2 (B)
unnamed: R14.2, SW2.2 (B)
unnamed: U3.9 (QH'), U4.14 (SER)
unnamed: R8.1, U5.2 (PROG)
unnamed: C14.2, L1.1, S3.1, U8.4 (EN), U8.5 (VIN)
unnamed: R15.2, R16.1, U8.3 (FB)
unnamed: C23.1, U11.4 (CAPM)
unnamed: C23.2, U11.2 (CAPP)
unnamed: C29.2, C31.2, U11.18 (LDOO)
unnamed: R22.1, U11.6 (OUTL)
unnamed: R23.1, U11.7 (OUTR)
unnamed: C24.2, C25.2, U11.5 (VNEG)
unnamed: R26.2, U12.35 (IO1/TXD0)
unnamed: R27.2, U12.34 (IO3/RXD0)
unnamed: C39.2, U13.4 (V3)
unnamed: C36.2, U13.7 (XI), Y1.1
unnamed: C37.2, U13.8 (XO), Y1.3
unnamed: C44.1, U14.17 (CPN)
unnamed: C44.2, U14.18 (CPP)
unnamed: C43.2, U14.15 (CPVSS_2), U14.16 (CPVSS)
unnamed: C35.1, U14.1 (LEFTINM)
unnamed: C34.1, U14.2 (LEFTINP)
unnamed: C32.2, U14.5 (RIGHTINM)
unnamed: C33.1, U14.4 (RIGHTINP)
PCM_L: C26.1, C27.1, R45.2
PCM_R: C28.1, C30.1, R44.2
RX0: R27.1, U13.2 (TXD)
SCL: R28.2, U1.14 (SCL), U9.7 (SDA), U10.6 (SCL), U12.36 (IO22/SCL), U14.8 (SCL)
SDA: R29.2, U1.15 (SDA), U9.8 (SCL), U10.5 (SDA), U12.33 (IO21/SDA), U14.7 (SDA)
SD_CS: J3.2 (CD/DAT3), U12.29 (IO5/V_CS)
SPI_CLK: J3.5 (CLK), U12.30 (IO18/V_CLK)
SPI_MISO: J3.7 (DAT0), U12.31 (IO19/V_MISO)
SPI_MOSI: J3.3 (CMD), U12.37 (IO23/V_MOSI)
STPUP_VIN: D3.1 (K), Q1.3 (D), S3.2, S3.3
TFT_CLK: TFT1.3 (SCK), U12.13 (IO14/H_CLK)
TFT_CS: TFT1.5 (CS), U12.23 (IO15/H_CS)
TFT_DC: TFT1.4 (D/C), U12.8 (IO32)
TFT_LED: Q2.3 (C), TFT1.10 (LED+)
TFT_MOSI: TFT1.6 (SDA(MOSI)), U12.16 (IO13/H_MOSI)
TFT_PWM: R24.2, U12.9 (IO33)
TX0: R26.1, U13.3 (RXD)
UD+: J1.A6 (D+), J1.B6 (D+), U13.5 (UD+)
UD-: J1.A7 (D-), J1.B7 (D-), U13.6 (UD-)
USB_SENS: R5.1, R6.2, U1.12 (P7)
Vin: C8.2, D3.2 (A), J1.A4 (VBUS), J1.A9 (VBUS), J1.B4 (VBUS), J1.B9 (VBUS), Q1.1 (G), R3.1, R4.1, R5.2, R9.1, U5.4 (V_{CC}), U5.8 (CE)
Vsens: R10.2, R11.1, U12.4 (SENSOR_VP/I36)

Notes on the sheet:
Extender
Battery & USB sense
TFT Display and brightness control
* In case of using external DAC: - solder all the components described in this block - do not populate R38, R39
ESP32 Module
* In case of using internal DAC: - do not solder components described in this block - populate R38, R39
RTC & EEPROM
Please note: in case of using CH340G please populate Y1, C36, C37
SD card
Turbosound
Audio AMP
USB UART
External DAC*
USB Charger and step-up
3.3v LDO
*R16 value should be adjusted to limit the charging current: 2k is for ~500mA
Controls
Audio Mixer
